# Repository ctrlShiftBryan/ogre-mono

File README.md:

# Ogre 68

A 68-key ergonomic keyboard, written by hand for
[ergogen](https://ergogen.xyz): key layout, board outline and a KiCad PCB, all
generated from one `ergogen/config.yaml`. It is a wireless split: one PCB per
half, each with its own nRF52840 module and power section on the board, laid
out for JLCPCB assembly.

34 keys a half: four staggered rows, a three-key inner column, a lone Esc
outboard of the number row, two arrow keys, and a four-key thumb cluster fanned
30°. Standard keycap sizes throughout — 1U alphas, 1.5U/1.75U/1.25U on the outer
column, 1.25U and 2.25U thumbs. `ergogen/README.md` describes the design;
`ergogen/ogre-ergo.keycaps.svg` renders it.

## Where it stands

- Layout, outline and PCBs all generate from the config: 68 keys on a 5x7
  matrix per half laid out for routing (the physical columns and rows, with
  the thumbs, arrows and Esc / Del fitted in), hotswap sockets
  with one diode per key, and an Ebyte E73 nRF52840 module with the nice!nano
  v2's power section on each half, all surface mount from JLC's parts library.
- The design's own values — column staggers, thumb fan, half separation — are
  named in the config's `units` block, so the board is tuned in one place.
- `npm run snapshot` holds the geometry against a committed baseline, so a key
  that moves without you meaning it fails.
- `npm run check` passes: wiring, every controller and power pin on its net,
  and KiCad DRC with no violations beyond the unrouted connections.
- **Next:** routing: a routed board as the copper master, with the build syncing
  placement into it. Mounting holes wait on the case.

## Working on it

```sh
cd ergogen && npm install
npm run serve     # live viewer on http://localhost:5174
```

The viewer watches `config.yaml` and `footprints/`, rebuilds on save and
refreshes itself: keycaps, points, outlines and the PCB, with the snapshot and
check scripts a button away. `ergogen/README.md` covers the other commands, the
PCB's matrix and break lines, and the ZMK changes the two removed keys imply.

## The rest of the repo

| Where | What |
|---|---|
| `ergogen/` | The Ogre 68: config, custom footprints, build and check scripts, live viewer |
| `layout/` | The 2019 Ogre Ergo's KLE design, its renderer, and an index of every KLE gist |
| `docs/ogre-repos.md` | Inventory of every Ogre repo — PCBs, firmware branches, tooling — and the project timeline |

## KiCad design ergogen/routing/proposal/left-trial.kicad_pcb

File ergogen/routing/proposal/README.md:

# Left-half placement proposal

Not yet the design: `config.yaml` still places the parts as before. This is a
proposal to review in KiCad before it's carried into the config.

- `left-placed.kicad_pcb`: every part placed, unrouted. The module's matrix
  pins are reassigned onto its outer-row pads (col0-col6 on 10 9 7 6 4 3 1,
  row0 17, row1 35, row2 15, row3 8, row4 2), J1 sits under Q and J2 under A
  with their plugs entering sideways, and the support parts cluster at their
  pins around the module.
- `left-trial.kicad_pcb`: the same board autorouted in one throwaway pass
  (every net but GND): 0 unrouted, 93 vias, 1 DRC nit. A check that the
  placement routes, not routing to keep.
- `place.py` made the placement from the build's board (greedy, each part at
  the free spot nearest what it connects to); `trial.py` made the trial route.

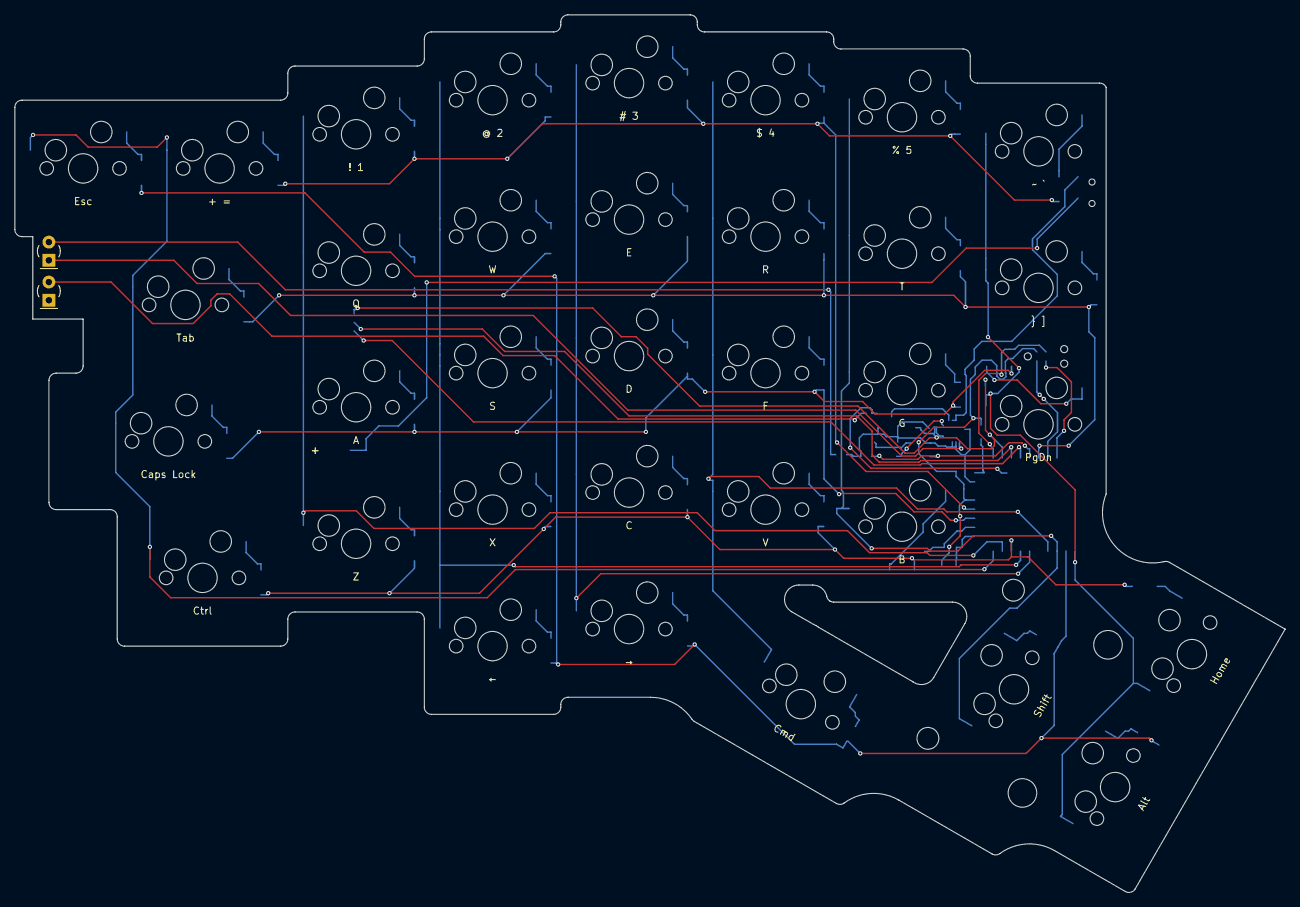
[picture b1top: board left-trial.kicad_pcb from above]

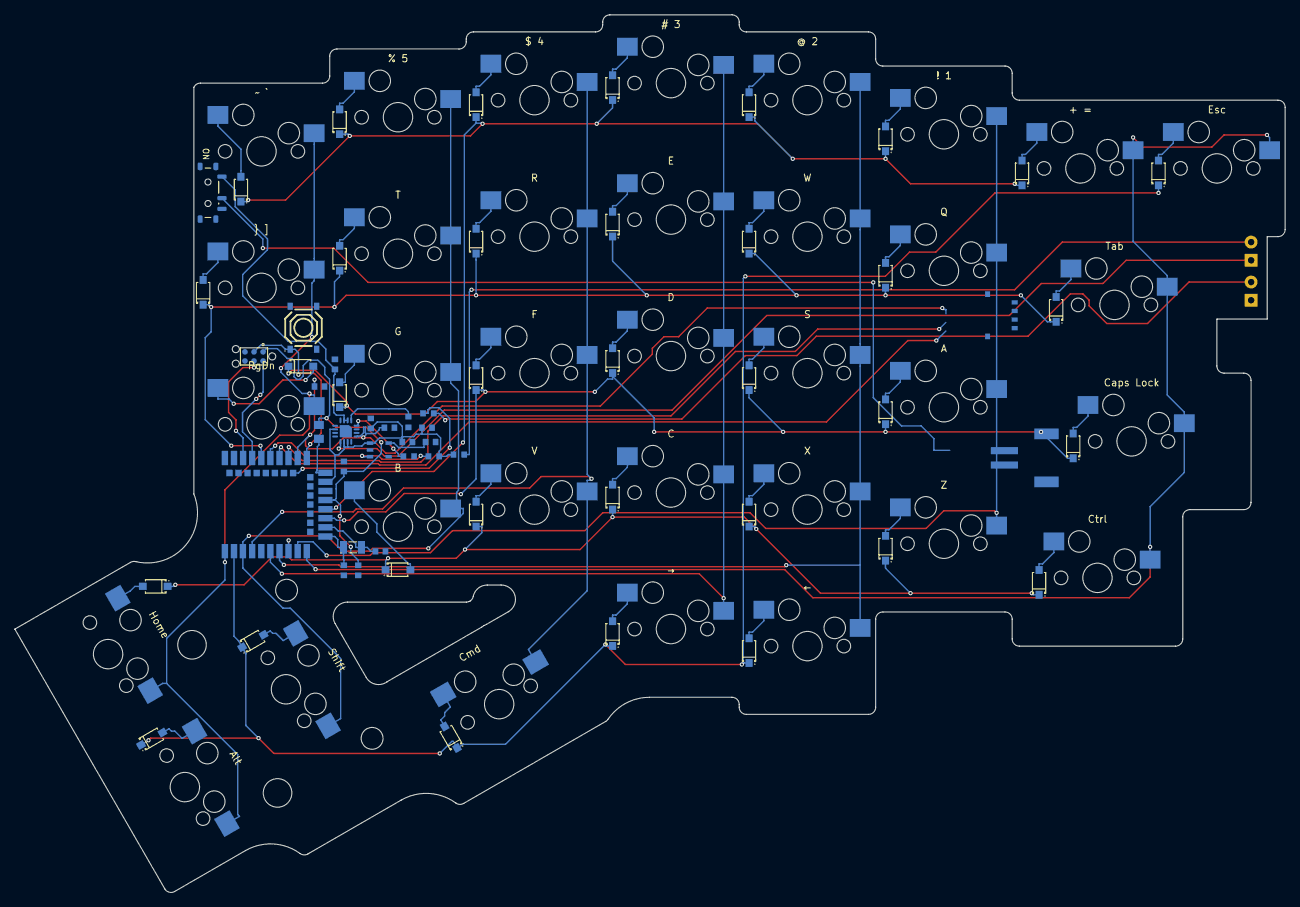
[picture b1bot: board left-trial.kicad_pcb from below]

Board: 2 copper layers, 177.3 x 122.5 mm, 130 parts (94 on the bottom side), 68 nets.

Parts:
C1, C3, C4, C8, C9, C11: 4.7uF; C_0603
C2: 100nF; C_0603
C5, C6: 12pF; C_0603
C7: 1uF; C_0603
C10: 10uF; C_0603
D1, D2, D3, D4, D5, D6, D7, D8, D9, D10, D11, D12, D13, D14, D15, D16, D17, D18, D19, D20, D21, D22, D23, D24, D25, D26, D27, D28, D29, D30, D31, D32, D33, D34: 1N4148W; Socket_Diode
IC1: BQ24075RGTR; BQ24075
IC2: XC6220B331MR-G; XC6220
J1: USB; USB_PicoEZmate
J2: BAT; JST_PH_S2B-PH-SM4
J3: SWD; SWD_TC2030-NL
L1: 10uH; L_0805
LED1: STATUS; LED_3mm
LED2: CHARGE; LED_3mm
MCU1: E73-2G4M08S1C
MX1, MX2, MX3, MX4, MX5, MX6, MX7, MX8, MX9, MX10, MX11, MX12, MX13, MX14, MX15, MX16, MX17, MX18, MX19, MX20, MX21, MX22, MX23, MX24, MX25, MX26, MX27, MX28, MX29, MX30, MX31, MX32, MX33, MX34: CherryMX_Hotswap
R1, R2: 1k; R_0603
R3, R4: 10k; R_0603
R5: 10M; R_0603
S1, S2, S3, S4, S5, S6, S7, S8, S9, S10, S11, S12, S13, S14, S15, S16, S17, S18, S19, S20, S21, S22, S23, S24, S25, S26, S27, S28, S29, S30, S31, S32, S33, S34: CPG151101S11; Hotswap_Socket
SW1: RESET; SW_Reset_TS1187A
SW2: POWER; SW_SPDT_MSK12C02
Y1: 32.768kHz; Crystal_FC-135

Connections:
BAT: J2.1, SW2.2
BLED: MCU1.28, R1.1
CHG: IC1.9, LED2.1
D+: J1.3, MCU1.31
D-: J1.2, MCU1.29
DCCH: L1.1, MCU1.25
GND: C1.2, C2.2, C3.2, C4.2, C5.2, C6.2, C7.2, C8.2, C9.2, C10.2, C11.2, IC1.4, IC1.5, IC1.8, IC1.15, IC1.17, IC2.2, J1.4, J1.6, J1.7, J2.2, J3.5, LED1.1, MCU1.5, MCU1.21, MCU1.24, R3.2, R4.2, SW1.4
ISET: IC1.16, R4.1
LED_C: LED2.2, R2.2
LED_S: LED1.2, R1.2
PWR_EN: IC2.3, MCU1.33, R5.2
RESET: J3.3, MCU1.26, SW1.1
SWDCLK: J3.4, MCU1.39
SWDIO: J3.2, MCU1.37
TS: IC1.1, R3.1
VBAT: C9.1, IC1.2, IC1.3, SW2.1
VBUS: C4.1, C7.1, IC1.13, J1.1, MCU1.27
VCC: C11.1, IC2.5
VDD: C1.1, C2.1, J3.1, L1.2, MCU1.19
VDDH: C3.1, C8.1, C10.1, IC1.6, IC1.10, IC1.11, IC2.1, MCU1.23, R2.1, R5.1
XL1: C5.1, MCU1.11, Y1.1
XL2: C6.1, MCU1.13, Y1.2
col0: MCU1.10, S1.1, S2.1, S3.1, S4.1, S5.1
col1: MCU1.9, S6.1, S7.1, S8.1, S9.1
col2: MCU1.7, S10.1, S11.1, S12.1, S13.1, S14.1
col3: MCU1.6, S15.1, S16.1, S17.1, S18.1, S19.1
col4: MCU1.4, S20.1, S21.1, S22.1, S23.1, S31.1
col5: MCU1.3, S24.1, S25.1, S26.1, S27.1, S32.1
col6: MCU1.1, S28.1, S29.1, S30.1, S33.1, S34.1
matrix_extra_home: D28.2, S28.2
matrix_extra_num: D30.2, S30.2
matrix_extra_top: D29.2, S29.2
matrix_far_num: D1.2, S1.2
matrix_index_bottom: D20.2, S20.2
matrix_index_home: D21.2, S21.2
matrix_index_num: D23.2, S23.2
matrix_index_top: D22.2, S22.2
matrix_inner_bottom: D24.2, S24.2
matrix_inner_home: D25.2, S25.2
matrix_inner_num: D27.2, S27.2
matrix_inner_top: D26.2, S26.2
matrix_middle_bottom: D16.2, S16.2
matrix_middle_home: D17.2, S17.2
matrix_middle_mod: D15.2, S15.2
matrix_middle_num: D19.2, S19.2
matrix_middle_top: D18.2, S18.2
matrix_outer_bottom: D2.2, S2.2
matrix_outer_home: D3.2, S3.2
matrix_outer_num: D5.2, S5.2
matrix_outer_top: D4.2, S4.2
matrix_pinky_bottom: D6.2, S6.2
matrix_pinky_home: D7.2, S7.2
matrix_pinky_num: D9.2, S9.2
matrix_pinky_top: D8.2, S8.2
matrix_ring_bottom: D11.2, S11.2
matrix_ring_home: D12.2, S12.2
matrix_ring_mod: D10.2, S10.2
matrix_ring_num: D14.2, S14.2
matrix_ring_top: D13.2, S13.2
row0: D5.1, D9.1, D14.1, D19.1, D23.1, D27.1, D30.1, MCU1.17
row1: D4.1, D8.1, D13.1, D18.1, D22.1, D26.1, D29.1, MCU1.35
row2: D3.1, D7.1, D12.1, D17.1, D21.1, D25.1, D28.1, MCU1.15
row3: D2.1, D6.1, D11.1, D16.1, D20.1, D24.1, D34.1, MCU1.8
row4: D1.1, D10.1, D15.1, D31.1, D32.1, D33.1, MCU1.2
thumb_far_cluster: D33.2, S33.2
thumb_far_upper: D34.2, S34.2
thumb_home_cluster: D32.2, S32.2
thumb_near_cluster: D31.2, S31.2

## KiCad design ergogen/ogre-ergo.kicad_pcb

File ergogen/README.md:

# The Ogre 68 in ergogen

`config.yaml` is the whole board, written by hand for
[ergogen](https://ergogen.xyz): key layout, board outline and an unrouted
KiCad PCB. It needs ergogen 4.1+ and the custom footprints in `footprints/`.
On ergogen.xyz (or a local clone of `ergogen/ergogen-gui`), load it from GitHub
with the repo URL (it finds `ergogen/config.yaml` and `ergogen/footprints/`
itself); pasting the YAML alone won't work, because the footprints wouldn't
load. That web UI reads the pushed repo, not the working tree, and its local
file picker is a one-shot upload that brings no footprints; for local work
use `npm run serve` below.

| File | What it is |
|---|---|
| `config.yaml` | Layout, outline and PCB |
| `footprints/` | The switch, its socket and diode, the nRF52840 module, charger, LDO, passives, crystal, connectors, switches, LEDs and SWD pads on the board (`ogre_*.js`); the 2019 PCB-mount switch, diode, Pro Micro and TRRS jack, the nice!nano and the through-hole JST PH connector, available but not placed |
| `footprints/jlc/` | Footprints pulled verbatim from JLCPCB's parts library with easyeda2kicad, one per assembled part, each carrying its LCSC number; `jlc.js` turns them into ergogen footprints |
| `serve.js` | Live viewer: watches the config, rebuilds and shows every view |
| `bundle.js` | Packs the config and footprints into an archive the web UI can open |
| `points.snapshot.json` | Baseline geometry for `npm run snapshot` |
| `ogre-ergo.keycaps.svg` | Key preview |
| `ogre-ergo.keycaps-print.svg` | The same keys for printing: white caps, black type, 1:1 in mm |

## The design

Everything that shapes the board is named in the config's `units` block. The
zones below it place keys and give them legends; the shape lives in `units`.

- **34 keys a half.** Four rows across six columns (outer, pinky, ring, middle,
  index, inner), a three-key extra column inboard of them, a lone Esc on the far
  column, two arrow keys below ring and middle, and four thumb keys.
- **Column stagger.** Each column steps against the one before it, and the
  steps add up to the profile across the hand: the middle column is highest at
  +0.375U, falling away to the pinky on one side and the inner and extra
  columns on the other. `stagger_far` through `stagger_extra`.
- **Key sizes.** 1U throughout, except the outer column's wide caps —
  1.5U Tab, 1.75U Caps Lock, 1.25U Ctrl — right-aligned to the pinky column.
- **Thumb cluster.** Three columns fanned `thumb_splay` (−30°) off the bottom
  of the middle column: 1.25U Cmd, 2.25U Shift, then 1.25U Alt with a 1U Home
  above it. The wide thumb caps are drawn as wide keys turned 90°, so switch
  and stabilizer footprints face the right way.
- **Halves.** Mirrored about an axis `half_spread` (4.25U) right of the extra
  column, which sets the gap between them.

## Legends

Each key has a `legend`: what's printed on a standard keycap set, not the
firmware keymap. `mirror.legend` is the legend of the matching key on the
right half, since ergogen builds the right half by mirroring the left. The PCB
prints each legend on both silkscreens, under its switch (readable from the
back once the switches are in).

Two-part legends are written shifted character first, then base, separated by
a space: `'! 1'` is the key with `!` over `1`. Anything else (`Esc`,
`Caps Lock`, `←`) is a single legend.

## The PCB

Two boards, always split, one per half: `left` and `right`, each its own KiCad
PCB with its own nets. Wireless only, with the controller on the board itself:
an nRF52840 module and the nice!nano v2's power section, all surface mount on
the back, for JLCPCB assembly. The matrix comes from the 2019 Ogre Ergo, where
it was fabricated and worked; the switch footprint from the 2024 rework
(`ogre.2024.pretty`); everything JLC places uses JLC's own footprint
(`footprints/jlc/`), so the pads and orientation match their line.

- **Key numbers.** Each half numbers its keys 1–34 in points order: up each
  column from the outer edge inward, then the thumbs. Key *n* on a half is that
  board's switch MX*n*, socket S*n* and diode D*n*. The keycap render
  (`ogre-ergo.keycaps.svg`, and the viewer's Keycaps tab) prints each key's
  number as L*n* or R*n*, and `npm run check` fails if a part is numbered out
  of step with its key.
- **One 10×7 matrix, one hotswap socket and one diode per key**, COL2ROW. The
  switch (`ogre_hotswap`) is holes, cap outline and legend; its copper is the
  socket (`ogre_socket`, a Kailh-compatible MX socket, JLC's clone) and the
  1N4148W diode in SOD-123F (`ogre_socket_diode`), each a part of its own on
  the back so it can be moved clear of traces. The socket places itself over
  the switch's pins; a key's `diode: [x, y, r]` in the zones places its diode
  (mm from the key, in its frame, y up; `mirror.diode` for the right half),
  and without one it sits at the switch's right edge, where the 2024 footprint
  had it built in. The 2.25U thumb keys add stabilizer holes (a key's `stab`),
  and a key's `turn` would turn its switch and socket together (no key uses it
  now). The grid is laid out for routing, five rows by seven columns:

  |          | col0 | col1 | col2 | col3 | col4 | col5  | col6 |
  |----------|------|------|------|------|------|-------|------|
  | **row0** | + =  | 1    | 2    | 3    | 4    | 5     | ~ \` |
  | **row1** | Tab  | Q    | W    | E    | R    | T     | } ]  |
  | **row2** | Caps | A    | S    | D    | F    | G     | PgDn |
  | **row3** | Ctrl | Z    | X    | C    | V    | B     | Home |
  | **row4** | Esc  |      | ←    | →    | Cmd  | Shift | Alt  |

  Each column net runs down a physical column, col0 the outer column through
  col6 the extra column, and each thumb key joins the column above it. Rows
  0–3 are the physical rows, with Home filling the extra column's empty bottom
  spot, and row4 gathers the rest: Esc, the arrows and the other thumbs. The
  right half is the same grid, mirrored (Del, End, Fn, Enter), on rows 5–9.
  Each half is its own PCB with its own nets, so the numbering across both is
  a convention, not a wire.
- **The controller** (MCU1): an Ebyte E73-2G4M08S1C, an nRF52840 module with
  its antenna, matching and crystals inside, lying sideways on the back below
  the extra column's home key (PgDn / `" '`), where that column has no bottom
  key, with its ceramic antenna end just inside the half's inner edge. Keep
  copper off that end on both layers; the diodes of the two keys beside it are
  moved out of its way in the zones. Its pin map is in `footprints/ogre_e73.js`: the seven
  columns on P1.10 P0.03 P0.28 P1.13 P0.02 P0.29 P0.31 (module pins
  2–9), the half's five rows on P0.30 P0.26 P0.06 P0.05 P0.08 (pins
  10–16; P1.11 on pin 1 and P1.09 on pin 17 are free), and the nice!nano's roles kept on the
  nice!nano's pins, so ZMK's `nice_nano_v2` configuration carries over with
  the matrix pins renamed: P0.13 cuts the LDO (`PWR_EN`), P0.15 drives the
  status LED (`BLED`), P0.18 is reset, battery voltage is read from VDDH.
- **Power, as on the nice!nano v2.** The battery (BAT) goes through the slide
  switch (VBAT) into a TI BQ24075 charger and power path (IC1): USB on IN,
  the battery on BAT, and OUT (VDDH) feeds the module in high-voltage mode,
  from USB when it's plugged in and the battery otherwise. 500 mA from USB
  (EN1 high, EN2 low), charging whenever USB is there (CE low, SYSOFF low),
  charge current set by the 10k on ISET (about 100 mA; a smaller resistor
  raises it), the thermistor faked with 10k on TS. The module's own regulator
  puts 3.3 V out on DCCH, which L1 (10 µH) carries to VDD. A Torex XC6220 LDO
  (IC2) makes VCC from VDDH for anything the board powers besides the module
  (LED strips, one day); its CE is pulled up to VDDH through 10 MΩ and driven
  by P0.13 (`PWR_EN`), so firmware can cut it. A 32.768 kHz crystal (Y1, FC-135)
  with 12 pF caps is the low-frequency clock. Nets and values are checked by
  `npm run check`.
- **USB** comes over a one-to-one 4-pin cable from a Unified Daughterboard S1
  ([unified-daughterboard.github.io](https://unified-daughterboard.github.io/))
  mounted in the case, which carries the USB-C port, its fuse and ESD
  protection. The board's end is a Molex Pico-EZmate (J2, 78171-0004) with the
  daughterboard's pinout, 1 VBUS 2 D− 3 D+ 4 GND, below S (L on the right),
  opening toward the index column.
- **Battery connector** (J2): a JST PH 2-pin side-entry surface-mount connector
  (S2B-PH-SM4-TB) below Q (P on the right), the plug entering from the outer
  edge's side, + on BAT and − on GND. JST sets no polarity. Pad 1 is +, the Adafruit and
  SparkFun convention (the battery plug's mating face toward you, polarizing
  bump up: red on the right), which the community wireless Corne also uses;
  the silkscreen marks it. About half of generic LiPos come wired the other
  way: check a new battery against that picture (or a multimeter) and swap its
  crimps, or set the connector's `plus` to 2.
- **Power switch** (SW2): a Shouhan MSK-12C02 side-actuated SPDT slide switch
  (pin-compatible with the Alps SSSS811101 the community wireless Corne uses),
  on the half's inner edge below `~ \`` (PgUp on the right), lever out past
  it. BAT comes in on the common pin 2, VBAT goes out on pin 1
  when on (the silkscreen marks that end ON), and pin 3 is left open, as on
  the Corne.
- **Reset** (SW1): a 5.1 mm surface-mount tactile switch (TS-1187A) below
  `~ \`` (PgUp on the right), beside that key's diode, wired across its
  diagonal pads so it works whichever way its pin pairs run.
- **SWD** (J3): six bare pads and three locating holes for a Tag-Connect
  TC2030-NL cable, under T / Y. The module arrives blank; this is how the UF2
  bootloader gets on once (any SWD probe; a Raspberry Pi Pico running
  debugprobe will do).
- **LEDs**: two 3 mm through-hole LEDs on the front, soldered by hand, on a tab
  below Esc (Del on the right) so they shine up through a hole in the case
  just below that key, one above the other: LED2 the charge LED (VDDH through
  1k, sinking into the charger's CHG, orange) and, below it, LED1 the status
  LED (P0.15 through 1k, blue). Each stands with its two pads in a line down
  the tab, the flat side (cathode) at the footprint's origin and the anode
  above it, so a bent-over LED shines sideways.
- **Where the rest sits.** Nothing juts out of the outline for the controller:
  the parts hide on the back in the 10 mm strips between one key's socket and
  the next key's switch pins. The module's inductor, capacitors and the crystal
  are in the strip between G and B, next to the module's pad end; the charger
  and LDO with their passives in the strip between `} ]` and PgDn; the SWD
  pads under T, between that switch's side pins; the USB connector below S,
  the battery connector below Q, and reset and the power switch below `~ \``,
  the switch on the inner edge, as placed in KiCad. Each is placed from a nearby key in
  the config (`mcu_x` / `mcu_y` for the module) and the right half reuses the
  same placement from the mirrored key. The config's numbers are a working
  first layout, not a final one: move parts in KiCad and carry them back (see
  `AGENTS.md`).
- **Outline:** keycap edges with 1 mm corners, thumbs included. The thumb
  cluster joins the matrix by filling only the gaps between neighboring keys
  (`thumb_web`), and one pocket per half is cut out over Cmd, as on the 2019
  board. Each half's inner edge runs straight up just inside its inner column,
  and the LED tab (`led_tab_w`, `led_tab_h`) hangs below Esc / Del. The `left`
  and `right` outlines are the halves; `board` is both together, for viewing.
- **No underglow LEDs**, no alternate-size switch footprints, and no mounting
  holes yet (see below).

### Ordering from JLCPCB

Every part JLC places carries its LCSC number as a footprint property
(`LCSC Part`), read from the footprint file in `footprints/jlc/` or set per
part in the config (the passives). The three hand-soldered footprints, the
switch outline, the LEDs and the SWD pads, carry none, and `npm run check`
holds that line. The bill of materials and placement files come out of the
routed board with KiCad's Fabrication Toolkit plugin (or Bouni's
kicad-jlcpcb-tools), which reads that property; the sockets and diodes sit on
the back with everything else, so assembly is single-sided. The module needs
JLC's Standard assembly tier and X-ray inspection. Stock on the module is the
one thing that can hold an order up: buy it into the JLC parts library early.

Both boards sit on KiCad's page at their `pcbs.<half>.params.origin` in the
config: after ergogen runs, `build.js` moves each finished PCB there as a whole
and puts KiCad's drill origin at the same spot. Ergogen's own coordinates (the
points, the snapshot, the reference DXFs) stay where they were.

Routing is left for KiCad. The PCBs are build output, not committed files:
`npm run build` writes `output/pcbs/left.kicad_pcb` and `right.kicad_pcb`, each
with a `.kicad_pro` beside it so KiCad opens it as a project. Every build
rewrites the boards in place (never deleting them, so KiCad can keep one open)
and leaves the project files and KiCad's other files alone; anything done to a
board in KiCad is replaced, so route in a copy. The projects have no schematic;
the board and its nets are the whole design.

The copy is `routing/left.kicad_pcb` (left half only, for now), committed: the
build's board with the parts not yet placed parked off its right edge. Routing
goes one section at a time: `python3 route.py <section>` leaves every pad
outside that section's parts and nets unconnected for the run, locks the
traces already there, runs [Freerouting](https://github.com/freerouting/freerouting)
headless (its jar in `~/.local/share/freerouting/`, or `FREEROUTING` set to
it), brings its traces into the board and reports what's still unrouted and
any DRC errors. The sections are listed in `route.py`; `matrix` is the
switches' columns, rows and diodes. The script also corrects two things
Freerouting gets wrong from KiCad's export: clearance to the curved board
edge, and hole keepouts on the turned thumb keys (see `fix_dsn`).

## Commands

```sh
npm install
npm run build    # write output/ (points, outlines, PCB)
npm run keycaps  # build, then render ogre-ergo.keycaps.svg with legends
npm run keycaps:print  # the same, black on white, as ogre-ergo.keycaps-print.svg
npm run snapshot # fail on geometry that changed since the last baseline
npm run check    # check the generated PCB's parts, nets and KiCad DRC
npm run serve    # live viewer on http://localhost:5174
npm run bundle   # pack config + footprints into output/ogre-ergo.ekb for the web UI
npm run reference # output/reference-left.dxf / -right.dxf, to draw a new outline over
npm run kicad    # build, then open a half's KiCad project (npm run kicad right)
```

`npm run kicad` opens `output/pcbs/left.kicad_pro` in KiCad (`npm run kicad
right` for the other half), to look the board over, run DRC or place parts. Placements made there come back by hand into
`config.yaml` (see `AGENTS.md`); everything else on the board is replaced by the
next build. After a rebuild (`npm run serve` rebuilds on every save), **File >
Revert** in the PCB editor loads the new board.

`npm run reference` plots each built half to a DXF for a vector editor: board
edge on `Edge.Cuts`, keycaps on `User.Drawings`, and the courtyards of the
switches and reset switches on `F.Courtyard`
and `B.Courtyard`. Units are mm and the coordinates are ergogen's own, y up, so
a drawing that keeps them lines up with the config, and the two halves line up
with each other. It needs `kicad-cli`.

`build.js` runs ergogen with the footprints in `footprints/`. The ergogen CLI
only loads custom footprints from a folder, and this folder also holds
`node_modules`.

`npm run keycaps` runs `render_keycaps.py`, which needs Python 3 and PyYAML
(`pip install pyyaml`; on macOS with Homebrew's Python, which refuses a
plain `pip install` and has no `pyyaml` formula, use
`python3 -m pip install --user --break-system-packages pyyaml`). `npm run serve`
renders it too, so without PyYAML the viewer prints `No module named 'yaml'`
on every rebuild. It reads the `output/points/points.yaml` that ergogen
writes in debug mode and draws each key as a keycap with its legend: alphas
in cream, modifiers and arrows in grey, Esc and Enter in red. With `--print`
(`npm run keycaps:print`) every cap is white with black type on a white
page, and the SVG is sized in mm, so it prints at 1:1: 412 × 176 mm, on
tabloid (11 × 17 in) landscape.

`npm run snapshot` is the regression gate. It holds the build against
`points.snapshot.json` — position, rotation and size of all 68 keys — and fails
on any key that moved, appeared or went. A change you meant to make is a new
baseline: `npm run snapshot:update` rewrites the file and prints what it
accepted, and that file goes in the commit with the config change that caused
it.

`npm run serve` starts a viewer that watches `config.yaml` and `footprints/`,
rebuilds on save (about 0.4 s) and refreshes the browser by itself, so the
files in this folder stay the single source of truth. Tabs: **Keycaps** (the
`render_keycaps.py` render), **Points** (ergogen's demo), **Outline** (any
outline in `output/outlines/`) and **PCB** (rendered by `kicad-cli`, with a
layer picker; **edge + keycaps** lays every keycap over the board outline). Drag to pan, wheel to zoom about the pointer, double click (or
**fit**) to fit the pane. The `snapshot` and `check` buttons run those scripts
and print their output. A YAML or footprint error shows in a red bar and the last good
render stays up until the next good build. Nothing leaves the machine.

`npm run bundle` writes `output/ogre-ergo.ekb`, a zip holding `config.yaml`
and `footprints/` as they are in the working tree. The ergogen web UI opens it
under **From Local File**, footprints and all, so the PCB generates there too.
Loading a bare `config.yaml` instead gives the layout and outlines but no PCB,
since the footprints wouldn't come with it. The archive is a snapshot: edits
made in the web editor don't come back to these files, so re-run `npm run
bundle` after changing the config.

`npm run check` reads the generated PCB and fails unless every key has one
switch, one socket and one diode wired column → socket → diode → row, no two
keys share a matrix position, the module's pads carry the nets listed above,
the charger, LDO, crystal, passives, connectors, switches and LEDs are wired
as described, and every assembled part carries its LCSC number. If
`kicad-cli` is installed it also runs KiCad's DRC (overlapping parts, hole and
edge clearances) and fails on any violation other than the unrouted
connections and the switch pins that pass through their sockets' courtyards.

## Firmware notes

With the nRF52840 on the board, ZMK wants a board definition of its own rather
than a shield on `nice_nano_v2`. Start from ZMK's `nice_nano_v2` board files
(the same charger, regulator cut-off on P0.13, battery read from VDDH, status
LED on P0.15, external 32 kHz crystal). The matrix no longer matches the ZMK
`ogre_ergo` shield in `ctrlShiftBryan/zmk-config2` (`boards/shields/ogre_ergo/`)
or QMK's `ogre/ergo_split`: both are 5×7 too, but with the keys in
different spots.

- **kscan per half:** five rows on P0.30 P0.26 P0.06 P0.05 P0.08 and
  seven columns on P1.10 P0.03 P0.28 P1.13 P0.02 P0.29 P0.31, COL2ROW,
  so `diode-direction = "col2row"`.
- **Transform:** 5 rows × 14 columns, `col-offset = <7>` for the right half,
  the grid in the PCB section above: Esc (Del) is RC(4,0), the arrows
  RC(4,2) and RC(4,3), Cmd, Shift and Alt RC(4,4)–RC(4,6), Home (End)
  RC(3,6). 68 entries, in the same key order as the keycap render.
- **Bindings** carry over key by key; only their `RC` positions change.

## Not done yet

- **Mounting holes.** None yet. They sit at key corners, so they follow from
  the case, and the case is a new design too.
- **Routing**, in KiCad.

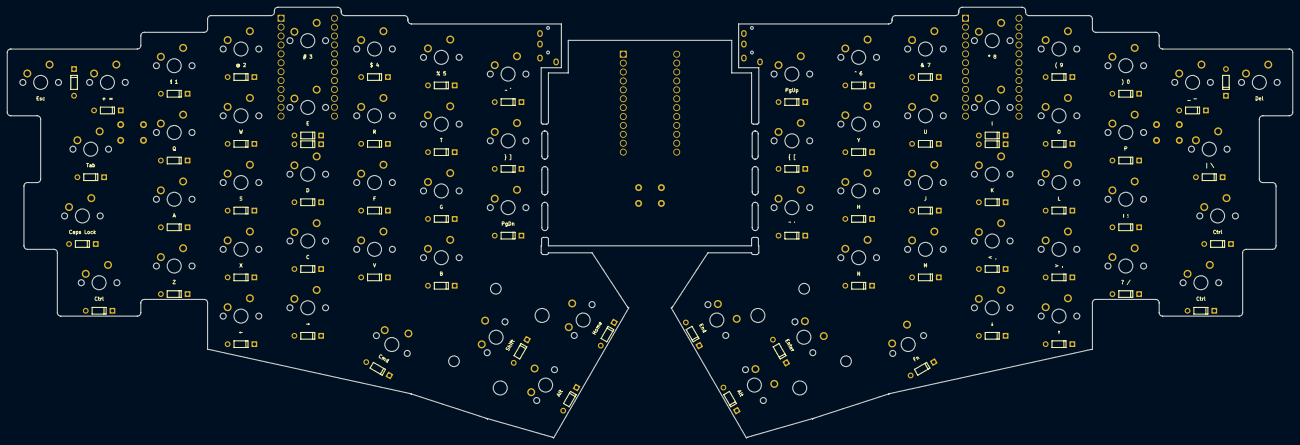
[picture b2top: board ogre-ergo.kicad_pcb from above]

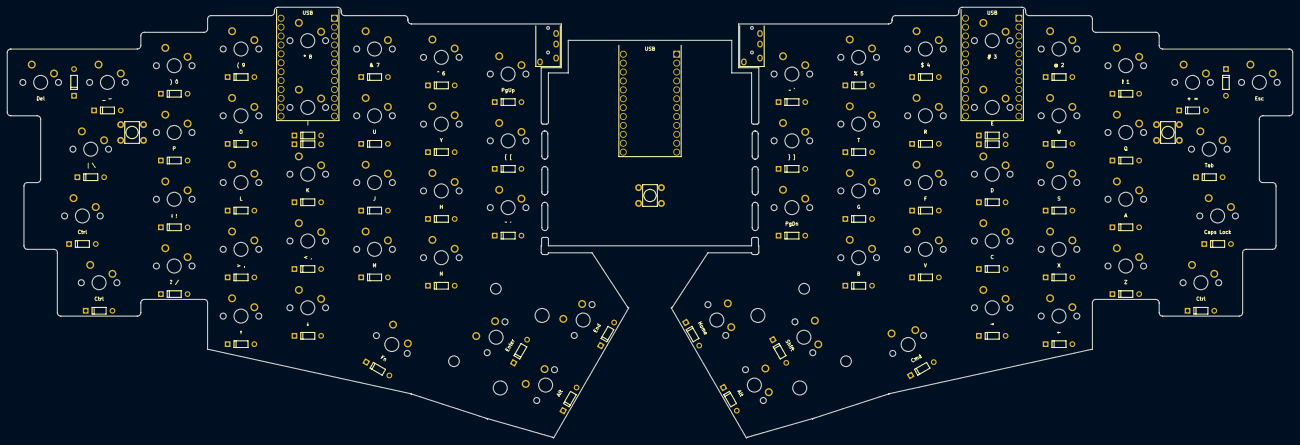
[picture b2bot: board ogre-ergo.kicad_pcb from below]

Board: 2 copper layers, 366.7 x 122.9 mm, 144 parts (5 on the bottom side), 94 nets, no tracks yet.

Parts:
D1, D2, D3, D4, D5, D6, D7, D8, D9, D10, D11, D12, D13, D14, D15, D16, D17, D18, D19, D20, D21, D22, D23, D24, D25, D26, D27, D28, D29, D30, D31, D32, D33, D34, D35, D36, D37, D38, D39, D40, D41, D42, D43, D44, D45, D46, D47, D48, D49, D50, D51, D52, D53, D54, D55, D56, D57, D58, D59, D60, D61, D62, D63, D64, D65, D66, D67, D68: Diode_THT
MCU1, MCU2, MCU3: ProMicro_MillMax
MX1, MX2, MX3, MX4, MX5, MX6, MX7, MX8, MX9, MX10, MX11, MX12, MX13, MX14, MX15, MX16, MX17, MX18, MX19, MX20, MX21, MX22, MX23, MX24, MX25, MX26, MX27, MX28, MX29, MX30, MX31, MX32, MX33, MX34, MX35, MX36, MX37, MX38, MX39, MX40, MX41, MX42, MX43, MX44, MX45, MX46, MX47, MX48, MX49, MX50, MX51, MX52, MX53, MX54, MX55, MX56, MX57, MX58, MX59, MX60, MX61, MX62, MX63, MX64, MX65, MX66, MX67, MX68: MX_PCB
SW1, SW2, SW3: SW_PUSH_6mm
TRRS1, TRRS2: TRRS_PJ-320A

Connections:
GND: MCU1.3, MCU1.4, MCU1.23, MCU2.3, MCU2.4, MCU2.23, MCU3.3, MCU3.4, MCU3.23, SW1.1, SW2.1, SW3.1, TRRS1.1, TRRS2.1
RESET0: MCU3.22, SW3.2
RESET1: MCU1.22, SW1.2
RESET2: MCU2.22, SW2.2
SCL1: MCU1.1, TRRS1.4
SCL2: MCU2.1, TRRS2.4
SDA1: MCU1.2, TRRS1.3
SDA2: MCU2.2, TRRS2.3
VCC: MCU1.21, MCU2.21, MCU3.21, TRRS1.2, TRRS2.2
col0: MCU1.20, MCU2.20, MCU3.20, MX2.1, MX3.1, MX4.1, MX5.1, MX35.1, MX36.1, MX37.1, MX38.1
col1: MCU1.19, MCU2.19, MCU3.19, MX6.1, MX7.1, MX8.1, MX9.1, MX33.1, MX39.1, MX40.1, MX41.1, MX42.1, MX66.1
col2: MCU1.18, MCU2.18, MCU3.18, MX10.1, MX11.1, MX12.1, MX13.1, MX14.1, MX43.1, MX44.1, MX45.1, MX46.1, MX47.1
col3: MCU1.17, MCU2.17, MCU3.17, MX15.1, MX16.1, MX17.1, MX18.1, MX19.1, MX48.1, MX49.1, MX50.1, MX51.1, MX52.1
col4: MCU1.16, MCU2.16, MCU3.16, MX20.1, MX21.1, MX22.1, MX23.1, MX31.1, MX53.1, MX54.1, MX55.1, MX56.1, MX64.1
col5: MCU1.15, MCU2.15, MCU3.15, MX24.1, MX25.1, MX26.1, MX27.1, MX57.1, MX58.1, MX59.1, MX60.1, MX67.1, MX68.1
col6: MCU1.14, MCU2.14, MCU3.14, MX1.1, MX28.1, MX29.1, MX30.1, MX32.1, MX34.1, MX61.1, MX62.1, MX63.1, MX65.1
matrix_extra_home: D26.2, MX28.2
matrix_extra_num: D28.2, MX30.2
matrix_extra_top: D27.2, MX29.2
matrix_far_num: D67.2, MX1.2
matrix_index_bottom: D18.2, MX20.2
matrix_index_home: D19.2, MX21.2
matrix_index_num: D21.2, MX23.2
matrix_index_top: D20.2, MX22.2
matrix_inner_bottom: D22.2, MX24.2
matrix_inner_home: D23.2, MX25.2
matrix_inner_num: D25.2, MX27.2
matrix_inner_top: D24.2, MX26.2
matrix_middle_bottom: D15.2, MX16.2
matrix_middle_home: D16.2, MX17.2
matrix_middle_mod: D14.2, MX15.2
matrix_middle_num: D65.2, MX19.2
matrix_middle_top: D17.2, MX18.2
matrix_outer_bottom: D1.2, MX2.2
matrix_outer_home: D2.2, MX3.2
matrix_outer_num: D4.2, MX5.2
matrix_outer_top: D3.2, MX4.2
matrix_pinky_bottom: D5.2, MX6.2
matrix_pinky_home: D6.2, MX7.2
matrix_pinky_num: D8.2, MX9.2
matrix_pinky_top: D7.2, MX8.2
matrix_ring_bottom: D10.2, MX11.2
matrix_ring_home: D11.2, MX12.2
matrix_ring_mod: D9.2, MX10.2
matrix_ring_num: D13.2, MX14.2
matrix_ring_top: D12.2, MX13.2
mirror_matrix_extra_home: D58.2, MX61.2
mirror_matrix_extra_num: D60.2, MX63.2
mirror_matrix_extra_top: D59.2, MX62.2
mirror_matrix_far_num: D68.2, MX34.2
mirror_matrix_index_bottom: D50.2, MX53.2
mirror_matrix_index_home: D51.2, MX54.2
mirror_matrix_index_num: D53.2, MX56.2
mirror_matrix_index_top: D52.2, MX55.2
mirror_matrix_inner_bottom: D54.2, MX57.2
mirror_matrix_inner_home: D55.2, MX58.2
mirror_matrix_inner_num: D57.2, MX60.2
mirror_matrix_inner_top: D56.2, MX59.2
mirror_matrix_middle_bottom: D47.2, MX49.2
mirror_matrix_middle_home: D48.2, MX50.2
mirror_matrix_middle_mod: D46.2, MX48.2
mirror_matrix_middle_num: D66.2, MX52.2
mirror_matrix_middle_top: D49.2, MX51.2
mirror_matrix_outer_bottom: D33.2, MX35.2
mirror_matrix_outer_home: D34.2, MX36.2
mirror_matrix_outer_num: D36.2, MX38.2
mirror_matrix_outer_top: D35.2, MX37.2
mirror_matrix_pinky_bottom: D37.2, MX39.2
mirror_matrix_pinky_home: D38.2, MX40.2
mirror_matrix_pinky_num: D40.2, MX42.2
mirror_matrix_pinky_top: D39.2, MX41.2
mirror_matrix_ring_bottom: D42.2, MX44.2
mirror_matrix_ring_home: D43.2, MX45.2
mirror_matrix_ring_mod: D41.2, MX43.2
mirror_matrix_ring_num: D45.2, MX47.2
mirror_matrix_ring_top: D44.2, MX46.2
mirror_thumb_far_cluster: D63.2, MX65.2
mirror_thumb_far_upper: D64.2, MX66.2
mirror_thumb_home_cluster: D62.2, MX68.2
mirror_thumb_near_cluster: D61.2, MX64.2
row0: D4.1, D8.1, D13.1, D21.1, D25.1, D28.1, D65.1, MCU1.8, MCU3.1
row1: D3.1, D7.1, D12.1, D17.1, D20.1, D24.1, D27.1, MCU1.9, MCU3.2
row2: D2.1, D6.1, D11.1, D16.1, D19.1, D23.1, D26.1, MCU1.10, MCU3.5
row3: D1.1, D5.1, D10.1, D15.1, D18.1, D22.1, D67.1, MCU1.11, MCU3.6
row4: D9.1, D14.1, D29.1, D30.1, D31.1, D32.1, MCU1.12, MCU3.7
row5: D36.1, D40.1, D45.1, D53.1, D57.1, D60.1, D66.1, MCU2.8, MCU3.8
row6: D35.1, D39.1, D44.1, D49.1, D52.1, D56.1, D59.1, MCU2.9, MCU3.9
row7: D34.1, D38.1, D43.1, D48.1, D51.1, D55.1, D58.1, MCU2.10, MCU3.10
row8: D33.1, D37.1, D42.1, D47.1, D50.1, D54.1, D68.1, MCU2.11, MCU3.11
row9: D41.1, D46.1, D61.1, D62.1, D63.1, D64.1, MCU2.12, MCU3.12
thumb_far_cluster: D31.2, MX32.2
thumb_far_upper: D32.2, MX33.2
thumb_home_cluster: D30.2, MX67.2
thumb_near_cluster: D29.2, MX31.2
